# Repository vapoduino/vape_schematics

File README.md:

# Open Source Vape schematics
This is the repository for the schematics of the open source vape.

It is based on Arduino and uses a MAX31865 for reading the temperature of a PT100 sensor.
For charging the LiPo batteries, a TP4056 is used.
The heat emitted by the heating wire is controled using a PH2925U mosfet.

There still are a lot of errors in this schematics, but you will get the general idea...

## Firmware
The Firmware can be found at [vapoduino/vape_firmware_arduino](https://github.com/vapoduino/vape_firmware_arduino)

## Model 
The model can be found at [vapoduino/vape_model](https://github.com/vapoduino/vape_model)

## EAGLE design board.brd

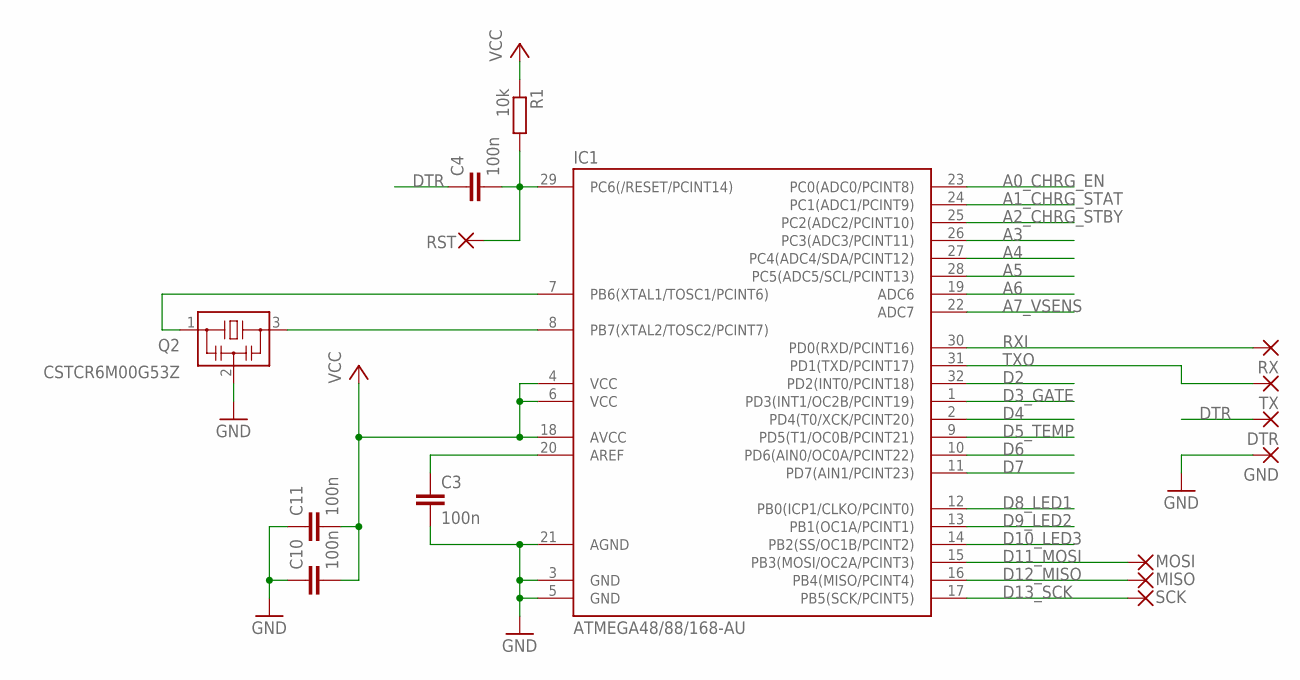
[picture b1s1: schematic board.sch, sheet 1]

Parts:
C3, C4, C10, C11: 100n; C0603
DTR: SMD2; SMD1,27-2,54
GND: SMD2; SMD1,27-2,54
IC1: ATMEGA48/88/168-AU; TQFP32-08
MISO: SMD2; SMD1,27-2,54
MOSI: SMD2; SMD1,27-2,54
Q2: CSTCR6M00G53Z; CSTCR6M
R1: 10k; R0603
RST: SMD2; SMD1,27-2,54
RX: SMD2; SMD1,27-2,54
SCK: SMD2; SMD1,27-2,54
TX: SMD2; SMD1,27-2,54

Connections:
A0_CHRG_EN: IC1.23 (PC0(ADC0/PCINT8)); also elsewhere on the board
A1_CHRG_STAT: IC1.24 (PC1(ADC1/PCINT9)); also elsewhere on the board
A2_CHRG_STBY: IC1.25 (PC2(ADC2/PCINT10)); also elsewhere on the board
A3: IC1.26 (PC3(ADC3/PCINT11))
A4: IC1.27 (PC4(ADC4/SDA/PCINT12))
A5: IC1.28 (PC5(ADC5/SCL/PCINT13))
A6: IC1.19 (ADC6)
A7_VSENS: IC1.22 (ADC7); also elsewhere on the board
AREF: C3.1, IC1.20 (AREF)
D2: IC1.32 (PD2(INT0/PCINT18))
D3_GATE: IC1.1 (PD3(INT1/OC2B/PCINT19)); also elsewhere on the board
D4: IC1.2 (PD4(T0/XCK/PCINT20))
D5_TEMP: IC1.9 (PD5(T1/OC0B/PCINT21))
D6: IC1.10 (PD6(AIN0/OC0A/PCINT22))
D7: IC1.11 (PD7(AIN1/PCINT23))
D8_LED1: IC1.12 (PB0(ICP1/CLKO/PCINT0)); also elsewhere on the board
D9_LED2: IC1.13 (PB1(OC1A/PCINT1)); also elsewhere on the board
D10_LED3: IC1.14 (PB2(SS/OC1B/PCINT2)); also elsewhere on the board
D11_MOSI: IC1.15 (PB3(MOSI/OC2A/PCINT3)), MOSI.1
D12_MISO: IC1.16 (PB4(MISO/PCINT4)), MISO.1
D13_SCK: IC1.17 (PB5(SCK/PCINT5)), SCK.1
DTR: C4.1, DTR.1
GND: C3.2, C10.1, C11.1, GND.1, IC1.3 (GND), IC1.5 (GND), IC1.21 (AGND), Q2.2; also elsewhere on the board
unnamed: IC1.8 (PB7(XTAL2/TOSC2/PCINT7)), Q2.3
RST: C4.2, IC1.29 (PC6(/RESET/PCINT14)), R1.2, RST.1
RXI: IC1.30 (PD0(RXD/PCINT16)), RX.1
TXO: IC1.31 (PD1(TXD/PCINT17)), TX.1
VCC: C10.2, C11.2, IC1.4 (VCC), IC1.6 (VCC), IC1.18 (AVCC), R1.1; also elsewhere on the board
XTAL1: IC1.7 (PB6(XTAL1/TOSC1/PCINT6)), Q2.1

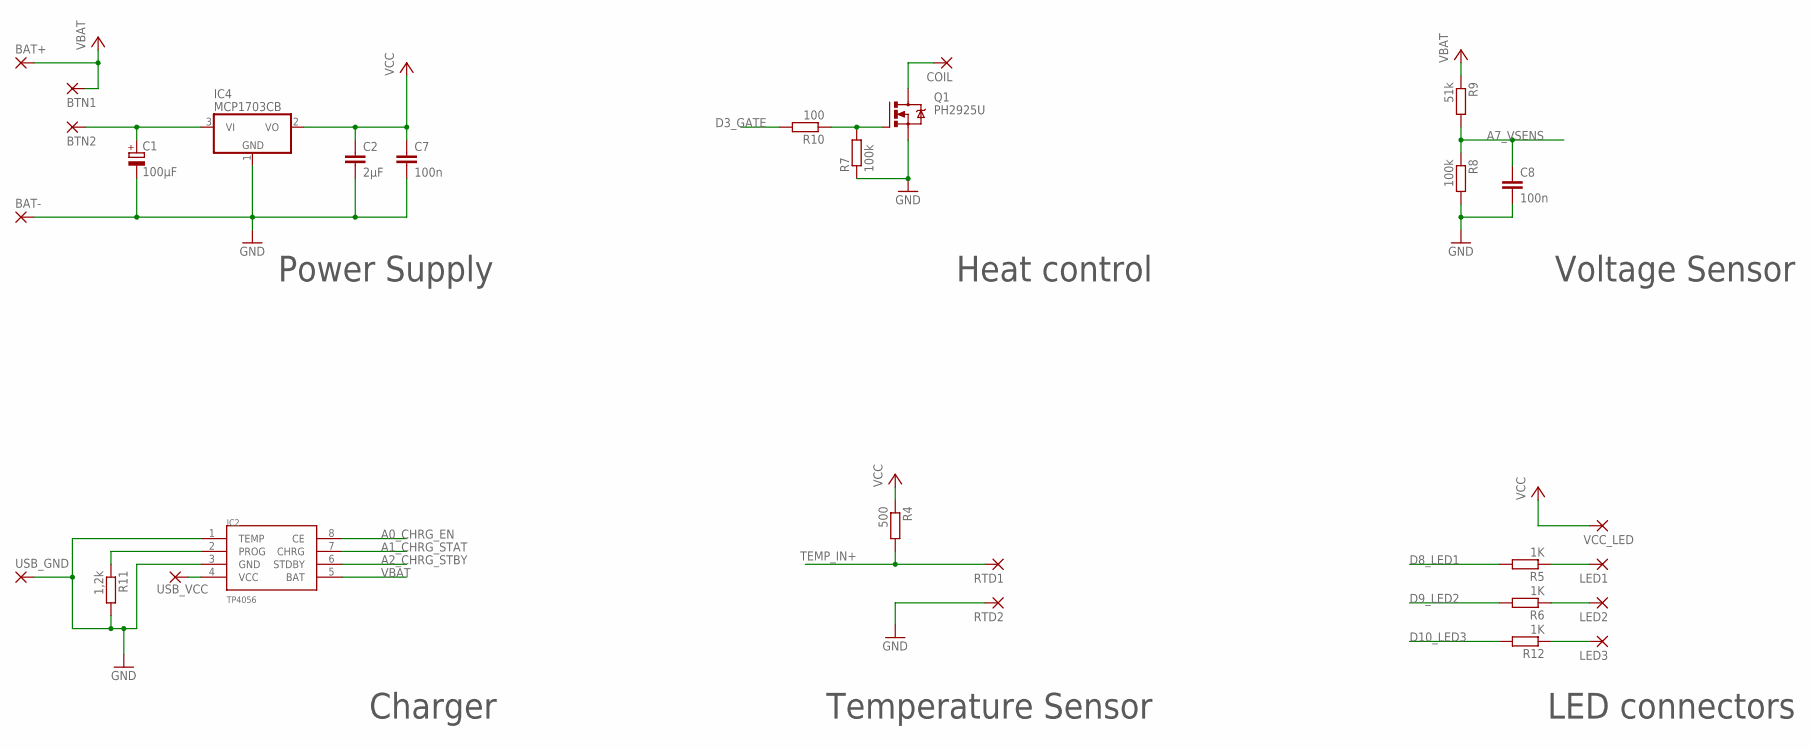
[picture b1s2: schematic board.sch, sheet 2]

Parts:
BAT+: SMD2; SMD1,27-2,54
BAT-: WIREPAD4,16O1,6; 4,16O1,6
BTN1, BTN2: SMD2; SMD1,27-2,54
C1: 100µF; CT7343
C2: 2µF; C1206
C7, C8: 100n; C0603
COIL: WIREPAD4,16O1,6; 4,16O1,6
IC2: TP4056; SOP-8
IC4: MCP1703CB; SOT23
LED1, LED2, LED3: SMD2; SMD1,27-2,54
Q1: PH2925U; SOT-669
R4: 500; R0603
R5, R6, R12: 1K; R0603
R7, R8: 100k; R0603
R9: 51k; R0603
R10: 100; R0603
R11: 1,2k; R0603
RTD1, RTD2: SMD2; SMD1,27-2,54
USB_GND: SMD2; SMD1,27-2,54
USB_VCC: SMD2; SMD1,27-2,54
VCC_LED: SMD2; SMD1,27-2,54

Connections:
A0_CHRG_EN: IC2.8 (CE); also elsewhere on the board
A1_CHRG_STAT: IC2.7 (CHRG); also elsewhere on the board
A2_CHRG_STBY: IC2.6 (STDBY); also elsewhere on the board
A7_VSENS: C8.1, R8.1, R9.2; also elsewhere on the board
COIL: COIL.1, Q1.5 (D)
D3_GATE: R10.2; also elsewhere on the board
D8_LED1: R5.2; also elsewhere on the board
D9_LED2: R6.2; also elsewhere on the board
D10_LED3: R12.2; also elsewhere on the board
GATE: Q1.4 (G), R7.2, R10.1
GND: BAT-.1, C1.-, C2.2, C7.2, C8.2, IC2.1 (TEMP), IC2.3 (GND), IC4.1 (GND), Q1.1 (S), Q1.2 (S), Q1.3 (S), R7.1, R8.2, R11.2, USB_GND.1; also elsewhere on the board
LED1: LED1.1, R5.1
LED2: LED2.1, R6.1
LED3: LED3.1, R12.1
PROG: IC2.2 (PROG), R11.1
TEMP_IN+: R4.2, RTD1.1
VBAT: BTN2.1, C1.+, IC2.5 (BAT), IC4.3 (VI), R9.1
VCC: BAT+.1, BTN1.1, C2.1, C7.1, IC4.2 (VO), R4.1, VCC_LED.1; also elsewhere on the board
VUSB: IC2.4 (VCC), USB_VCC.1

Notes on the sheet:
Power Supply
Charger
Heat control
Voltage Sensor
LED connectors
Temperature Sensor

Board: 2 copper layers, 44 parts (0 on the bottom side), 29 nets, no tracks yet.

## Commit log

2017-03-06 splitting into separated repositories
2017-03-06 cleanup of schematics
2017-06-17 using smaller resistors for voltage sensor
2017-06-22 using new mosfets, rearangement of parts
2017-07-26 adding 3rd LED, new regulator, shrinking board
2017-07-26 first draft of new layout
2017-07-27 adding vias for mosfet
2017-07-27 connect leds via bottom
2017-07-27 rearanging led and spi traces, adding vias for gnd and heat, checking layout, READY for production
2017-07-27 adding tstop for charger heat transfer
2017-08-28 using MCP1703 as vreg
2017-12-29 updating readme
2017-12-29 adding license file
2019-12-27 draft
